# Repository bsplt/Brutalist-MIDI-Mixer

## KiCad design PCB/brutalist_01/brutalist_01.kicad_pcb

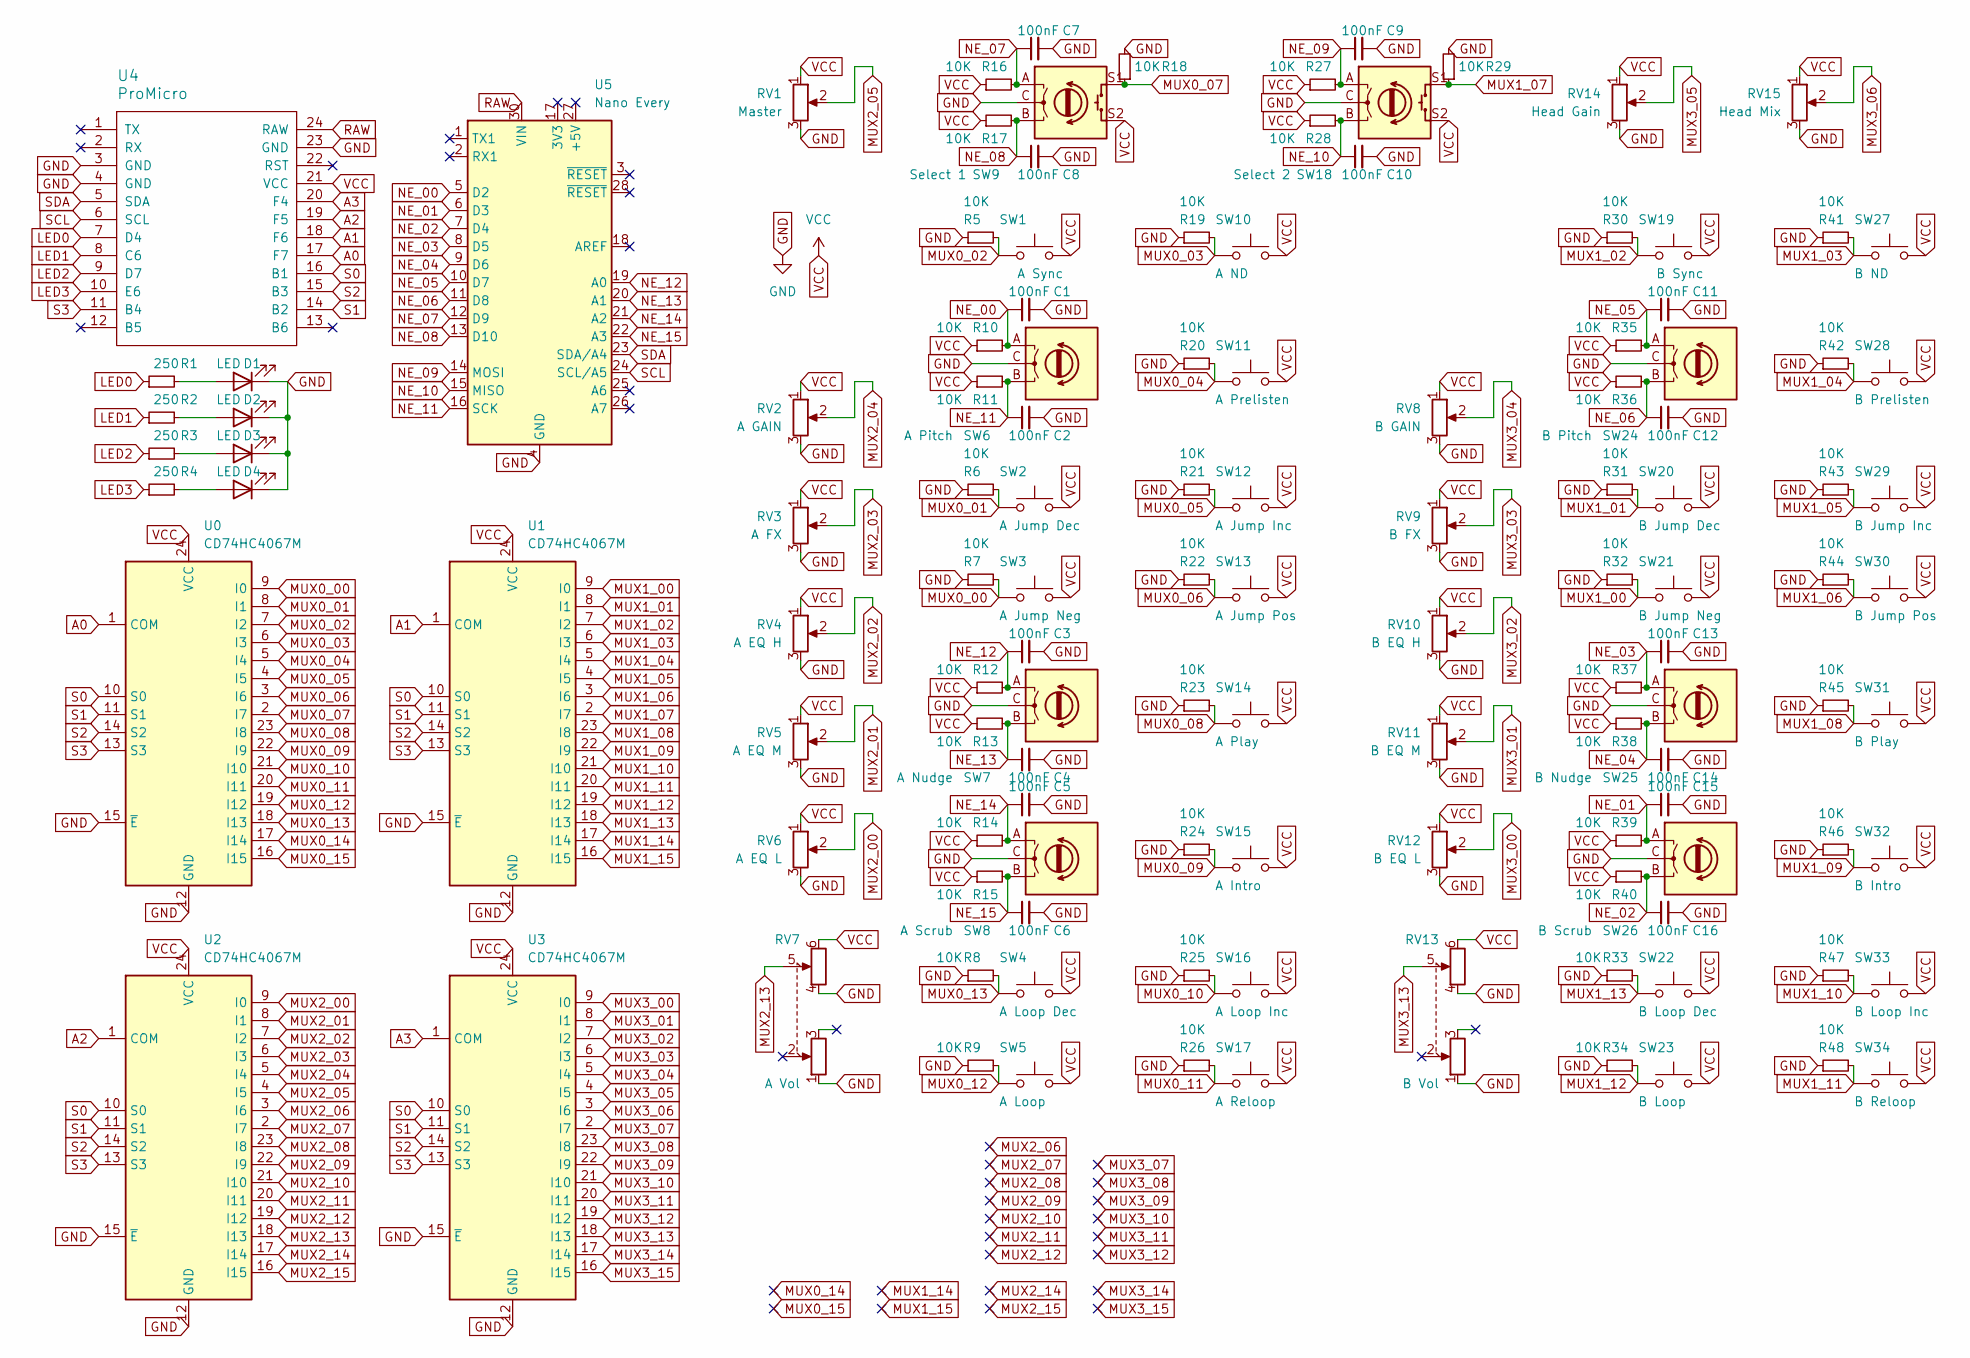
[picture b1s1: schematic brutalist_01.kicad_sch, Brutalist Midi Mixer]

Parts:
C1, C2, C3, C4, C5, C6, C7, C8, C9, C10, C11, C12, C13, C14, C15, C16: 100nF; C_Disc_D10.0mm_W2.5mm_P5.00mm
D1, D2, D3, D4: LED; LED_D5.0mm
R1, R2, R3, R4: 250; R_Axial_DIN0207_L6.3mm_D2.5mm_P10.16mm_Horizontal
R5, R6, R7, R8, R9, R10, R11, R12, R13, R14, R15, R16, R17, R18, R19, R20, R21, R22, R23, R24, R25, R26, R27, R28, R29, R30, R31, R32, R33, R34, R35, R36, R37, R38, R39, R40, R41, R42, R43, R44, R45, R46, R47, R48: 10K; R_Axial_DIN0207_L6.3mm_D2.5mm_P10.16mm_Horizontal
RV1: Master; Potentiometer_Alps_RK09K_Single_Vertical
RV2: A GAIN; Potentiometer_Alps_RK09K_Single_Vertical
RV3: A FX; Potentiometer_Alps_RK09K_Single_Vertical
RV4: A EQ H; Potentiometer_Alps_RK09K_Single_Vertical
RV5: A EQ M; Potentiometer_Alps_RK09K_Single_Vertical
RV6: A EQ L; Potentiometer_Alps_RK09K_Single_Vertical
RV7: A Vol; ALPS RS60112
RV8: B GAIN; Potentiometer_Alps_RK09K_Single_Vertical
RV9: B FX; Potentiometer_Alps_RK09K_Single_Vertical
RV10: B EQ H; Potentiometer_Alps_RK09K_Single_Vertical
RV11: B EQ M; Potentiometer_Alps_RK09K_Single_Vertical
RV12: B EQ L; Potentiometer_Alps_RK09K_Single_Vertical
RV13: B Vol; ALPS RS60112
RV14: Head Gain; Potentiometer_Alps_RK09K_Single_Vertical
RV15: Head Mix; Potentiometer_Alps_RK09K_Single_Vertical
SW1: A Sync; SW_Cherry_MX_1.00u_PCB_edit
SW2: A Jump Dec; SW_Cherry_MX_1.00u_PCB_edit
SW3: A Jump Neg; SW_Cherry_MX_1.00u_PCB_edit
SW4: A Loop Dec; SW_Cherry_MX_1.00u_PCB_edit
SW5: A Loop; SW_Cherry_MX_1.00u_PCB_edit
SW6: A Pitch; RotaryEncoder_Alps_EC12E_Vertical_H20mm
SW7: A Nudge; RotaryEncoder_Alps_EC12E_Vertical_H20mm
SW8: A Scrub; RotaryEncoder_Alps_EC12E_Vertical_H20mm
SW9: Select 1; RotaryEncoder_Alps_EC11E-Switch_Vertical_H20mm
SW10: A ND; SW_Cherry_MX_1.00u_PCB_edit
SW11: A Prelisten; SW_Cherry_MX_1.00u_PCB_edit
SW12: A Jump Inc; SW_Cherry_MX_1.00u_PCB_edit
SW13: A Jump Pos; SW_Cherry_MX_1.00u_PCB_edit
SW14: A Play; SW_Cherry_MX_1.00u_PCB_edit
SW15: A Intro; SW_Cherry_MX_1.00u_PCB_edit
SW16: A Loop Inc; SW_Cherry_MX_1.00u_PCB_edit
SW17: A Reloop; SW_Cherry_MX_1.00u_PCB_edit
SW18: Select 2; RotaryEncoder_Alps_EC11E-Switch_Vertical_H20mm
SW19: B Sync; SW_Cherry_MX_1.00u_PCB_edit
SW20: B Jump Dec; SW_Cherry_MX_1.00u_PCB_edit
SW21: B Jump Neg; SW_Cherry_MX_1.00u_PCB_edit
SW22: B Loop Dec; SW_Cherry_MX_1.00u_PCB_edit
SW23: B Loop; SW_Cherry_MX_1.00u_PCB_edit
SW24: B Pitch; RotaryEncoder_Alps_EC12E_Vertical_H20mm
SW25: B Nudge; RotaryEncoder_Alps_EC12E_Vertical_H20mm
SW26: B Scrub; RotaryEncoder_Alps_EC12E_Vertical_H20mm
SW27: B ND; SW_Cherry_MX_1.00u_PCB_edit
SW28: B Prelisten; SW_Cherry_MX_1.00u_PCB_edit
SW29: B Jump Inc; SW_Cherry_MX_1.00u_PCB_edit
SW30: B Jump Pos; SW_Cherry_MX_1.00u_PCB_edit
SW31: B Play; SW_Cherry_MX_1.00u_PCB_edit
SW32: B Intro; SW_Cherry_MX_1.00u_PCB_edit
SW33: B Loop Inc; SW_Cherry_MX_1.00u_PCB_edit
SW34: B Reloop; SW_Cherry_MX_1.00u_PCB_edit
U0, U1, U2, U3: CD74HC4067M; SOIC-24W_7.5x15.4mm_P1.27mm
U4: ProMicro
U5: Nano Every; Arduino_Nano

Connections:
A0: U0.1 (COM), U4.17 (F7)
A1: U1.1 (COM), U4.18 (F6)
A2: U2.1 (COM), U4.19 (F5)
A3: U3.1 (COM), U4.20 (F4)
GND: C1.2, C2.2, C3.2, C4.2, C5.2, C6.2, C7.2, C8.2, C9.2, C10.2, C11.2, C12.2, C13.2, C14.2, C15.2, C16.2, D1.1 (K), D2.1 (K), D3.1 (K), D4.1 (K), R5.1, R6.1, R7.1, R8.1, R9.1, R18.2, R19.1, R20.1, R21.1, R22.1, R23.1, R24.1, R25.1, R26.1, R29.2, R30.1, R31.1, R32.1, R33.1, R34.1, R41.1, R42.1, R43.1, R44.1, R45.1, R46.1, R47.1, R48.1, RV1.3, RV2.3, RV3.3, RV4.3, RV5.3, RV6.3, RV7.1, RV7.4, RV8.3, RV9.3, RV10.3, RV11.3, RV12.3, RV13.1, RV13.4, RV14.3, RV15.3, SW6.C, SW7.C, SW8.C, SW9.C, SW18.C, SW24.C, SW25.C, SW26.C, U0.12 (GND), U0.15 (~E), U1.12 (GND), U1.15 (~E), U2.12 (GND), U2.15 (~E), U3.12 (GND), U3.15 (~E), U4.3 (GND), U4.4 (GND), U4.23 (GND), U5.4 (GND), U5.29 (GND)
LED0: R1.1, U4.7 (D4)
LED1: R2.1, U4.8 (C6)
LED2: R3.1, U4.9 (D7)
LED3: R4.1, U4.10 (E6)
MUX0_00: R7.2, SW3.1, U0.9 (I0)
MUX0_01: R6.2, SW2.1, U0.8 (I1)
MUX0_02: R5.2, SW1.1, U0.7 (I2)
MUX0_03: R19.2, SW10.1, U0.6 (I3)
MUX0_04: R20.2, SW11.1, U0.5 (I4)
MUX0_05: R21.2, SW12.1, U0.4 (I5)
MUX0_06: R22.2, SW13.1, U0.3 (I6)
MUX0_07: R18.1, SW9.S1, U0.2 (I7)
MUX0_08: R23.2, SW14.1, U0.23 (I8)
MUX0_09: R24.2, SW15.1, U0.22 (I9)
MUX0_10: R25.2, SW16.1, U0.21 (I10)
MUX0_11: R26.2, SW17.1, U0.20 (I11)
MUX0_12: R9.2, SW5.1, U0.19 (I12)
MUX0_13: R8.2, SW4.1, U0.18 (I13)
MUX0_14: U0.17 (I14)
MUX0_15: U0.16 (I15)
MUX1_00: R32.2, SW21.1, U1.9 (I0)
MUX1_01: R31.2, SW20.1, U1.8 (I1)
MUX1_02: R30.2, SW19.1, U1.7 (I2)
MUX1_03: R41.2, SW27.1, U1.6 (I3)
MUX1_04: R42.2, SW28.1, U1.5 (I4)
MUX1_05: R43.2, SW29.1, U1.4 (I5)
MUX1_06: R44.2, SW30.1, U1.3 (I6)
MUX1_07: R29.1, SW18.S1, U1.2 (I7)
MUX1_08: R45.2, SW31.1, U1.23 (I8)
MUX1_09: R46.2, SW32.1, U1.22 (I9)
MUX1_10: R47.2, SW33.1, U1.21 (I10)
MUX1_11: R48.2, SW34.1, U1.20 (I11)
MUX1_12: R34.2, SW23.1, U1.19 (I12)
MUX1_13: R33.2, SW22.1, U1.18 (I13)
MUX1_14: U1.17 (I14)
MUX1_15: U1.16 (I15)
MUX2_00: RV6.2, U2.9 (I0)
MUX2_01: RV5.2, U2.8 (I1)
MUX2_02: RV4.2, U2.7 (I2)
MUX2_03: RV3.2, U2.6 (I3)
MUX2_04: RV2.2, U2.5 (I4)
MUX2_05: RV1.2, U2.4 (I5)
MUX2_06: U2.3 (I6)
MUX2_07: U2.2 (I7)
MUX2_08: U2.23 (I8)
MUX2_09: U2.22 (I9)
MUX2_10: U2.21 (I10)
MUX2_11: U2.20 (I11)
MUX2_12: U2.19 (I12)
MUX2_13: RV7.5, U2.18 (I13)
MUX2_14: U2.17 (I14)
MUX2_15: U2.16 (I15)
MUX3_00: RV12.2, U3.9 (I0)
MUX3_01: RV11.2, U3.8 (I1)
MUX3_02: RV10.2, U3.7 (I2)
MUX3_03: RV9.2, U3.6 (I3)
MUX3_04: RV8.2, U3.5 (I4)
MUX3_05: RV14.2, U3.4 (I5)
MUX3_06: RV15.2, U3.3 (I6)
MUX3_07: U3.2 (I7)
MUX3_08: U3.23 (I8)
MUX3_09: U3.22 (I9)
MUX3_10: U3.21 (I10)
MUX3_11: U3.20 (I11)
MUX3_12: U3.19 (I12)
MUX3_13: RV13.5, U3.18 (I13)
MUX3_14: U3.17 (I14)
MUX3_15: U3.16 (I15)
NE_00: C1.1, R10.2, SW6.A, U5.5 (D2)
NE_01: C15.1, R39.2, SW26.A, U5.6 (D3)
NE_02: C16.1, R40.2, SW26.B, U5.7 (D4)
NE_03: C13.1, R37.2, SW25.A, U5.8 (D5)
NE_04: C14.1, R38.2, SW25.B, U5.9 (D6)
NE_05: C11.1, R35.2, SW24.A, U5.10 (D7)
NE_06: C12.1, R36.2, SW24.B, U5.11 (D8)
NE_07: C7.1, R16.2, SW9.A, U5.12 (D9)
NE_08: C8.1, R17.2, SW9.B, U5.13 (D10)
NE_09: C9.1, R27.2, SW18.A, U5.14 (MOSI)
NE_10: C10.1, R28.2, SW18.B, U5.15 (MISO)
NE_11: C2.1, R11.2, SW6.B, U5.16 (SCK)
NE_12: C3.1, R12.2, SW7.A, U5.19 (A0)
NE_13: C4.1, R13.2, SW7.B, U5.20 (A1)
NE_14: C5.1, R14.2, SW8.A, U5.21 (A2)
NE_15: C6.1, R15.2, SW8.B, U5.22 (A3)
unnamed: D1.2 (A), R1.2
unnamed: D2.2 (A), R2.2
unnamed: D3.2 (A), R3.2
unnamed: D4.2 (A), R4.2
RAW: U4.24 (RAW), U5.30 (VIN)
S0: U0.10 (S0), U1.10 (S0), U2.10 (S0), U3.10 (S0), U4.16 (B1)
S1: U0.11 (S1), U1.11 (S1), U2.11 (S1), U3.11 (S1), U4.14 (B2)
S2: U0.14 (S2), U1.14 (S2), U2.14 (S2), U3.14 (S2), U4.15 (B3)
S3: U0.13 (S3), U1.13 (S3), U2.13 (S3), U3.13 (S3), U4.11 (B4)
SCL: U4.6 (SCL), U5.24 (SCL/A5)
SDA: U4.5 (SDA), U5.23 (SDA/A4)
VCC: R10.1, R11.1, R12.1, R13.1, R14.1, R15.1, R16.1, R17.1, R27.1, R28.1, R35.1, R36.1, R37.1, R38.1, R39.1, R40.1, RV1.1, RV2.1, RV3.1, RV4.1, RV5.1, RV6.1, RV7.6, RV8.1, RV9.1, RV10.1, RV11.1, RV12.1, RV13.6, RV14.1, RV15.1, SW1.2, SW2.2, SW3.2, SW4.2, SW5.2, SW9.S2, SW10.2, SW11.2, SW12.2, SW13.2, SW14.2, SW15.2, SW16.2, SW17.2, SW18.S2, SW19.2, SW20.2, SW21.2, SW22.2, SW23.2, SW27.2, SW28.2, SW29.2, SW30.2, SW31.2, SW32.2, SW33.2, SW34.2, U0.24 (VCC), U1.24 (VCC), U2.24 (VCC), U3.24 (VCC), U4.21 (VCC)

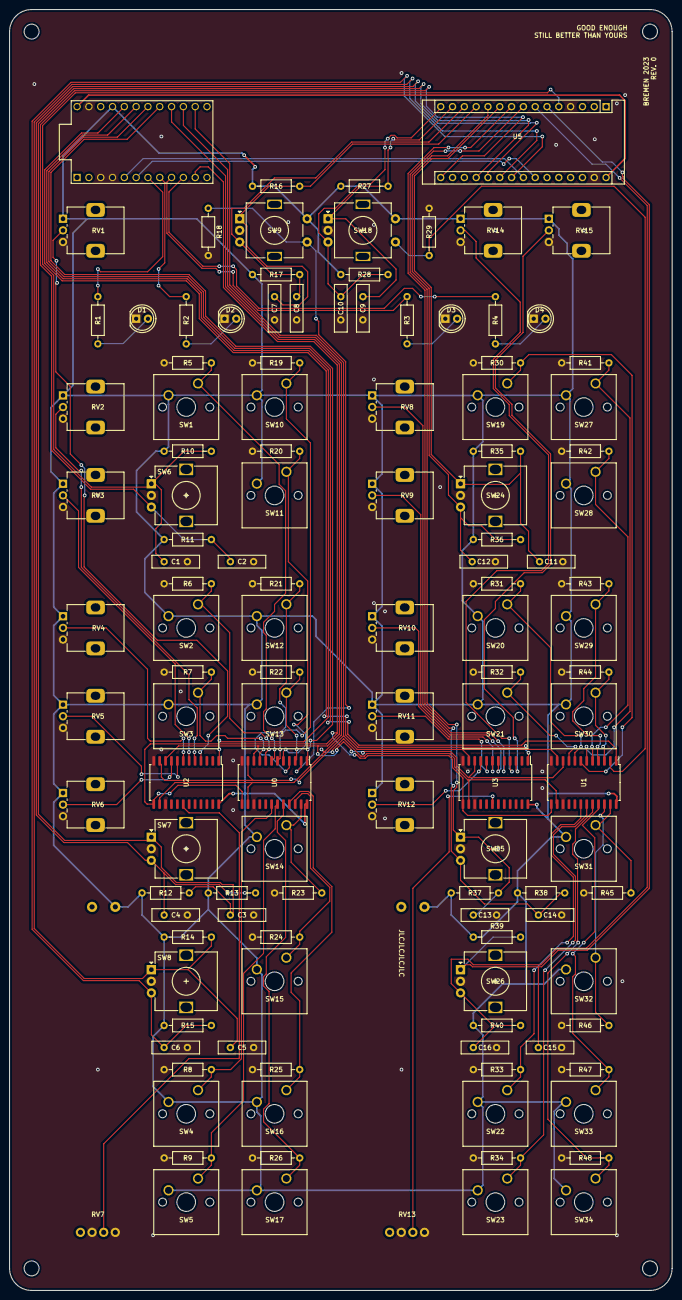
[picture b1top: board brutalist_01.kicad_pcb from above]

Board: 2 copper layers, 142.5 x 275.5 mm, 123 parts (0 on the bottom side), 80 nets.

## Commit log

2023-01-05 start infrastructure
2023-01-08 update schematic to nano
2023-01-09 update schematic
2023-01-09 update schematic
    maybe finished
2023-01-09 add slide potentiometer
2023-01-09 add footprints
2023-01-09 add custom mx footprint
2023-01-09 place components
2023-01-10 create traces for basic infrastructure
2023-01-10 finish routing
2023-01-10 add graphics
2023-01-10 generate gerbers
2023-01-19 create code
2023-01-20 create fundamental code for production
2023-01-22 update code
2023-01-23 finish firmware
2023-01-23 fix snap point
2023-01-23 add mixxx mapping
